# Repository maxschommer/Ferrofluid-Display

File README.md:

# Ferrofluid-Display
Ferrofluid Screen with capability of remote control boat driving.

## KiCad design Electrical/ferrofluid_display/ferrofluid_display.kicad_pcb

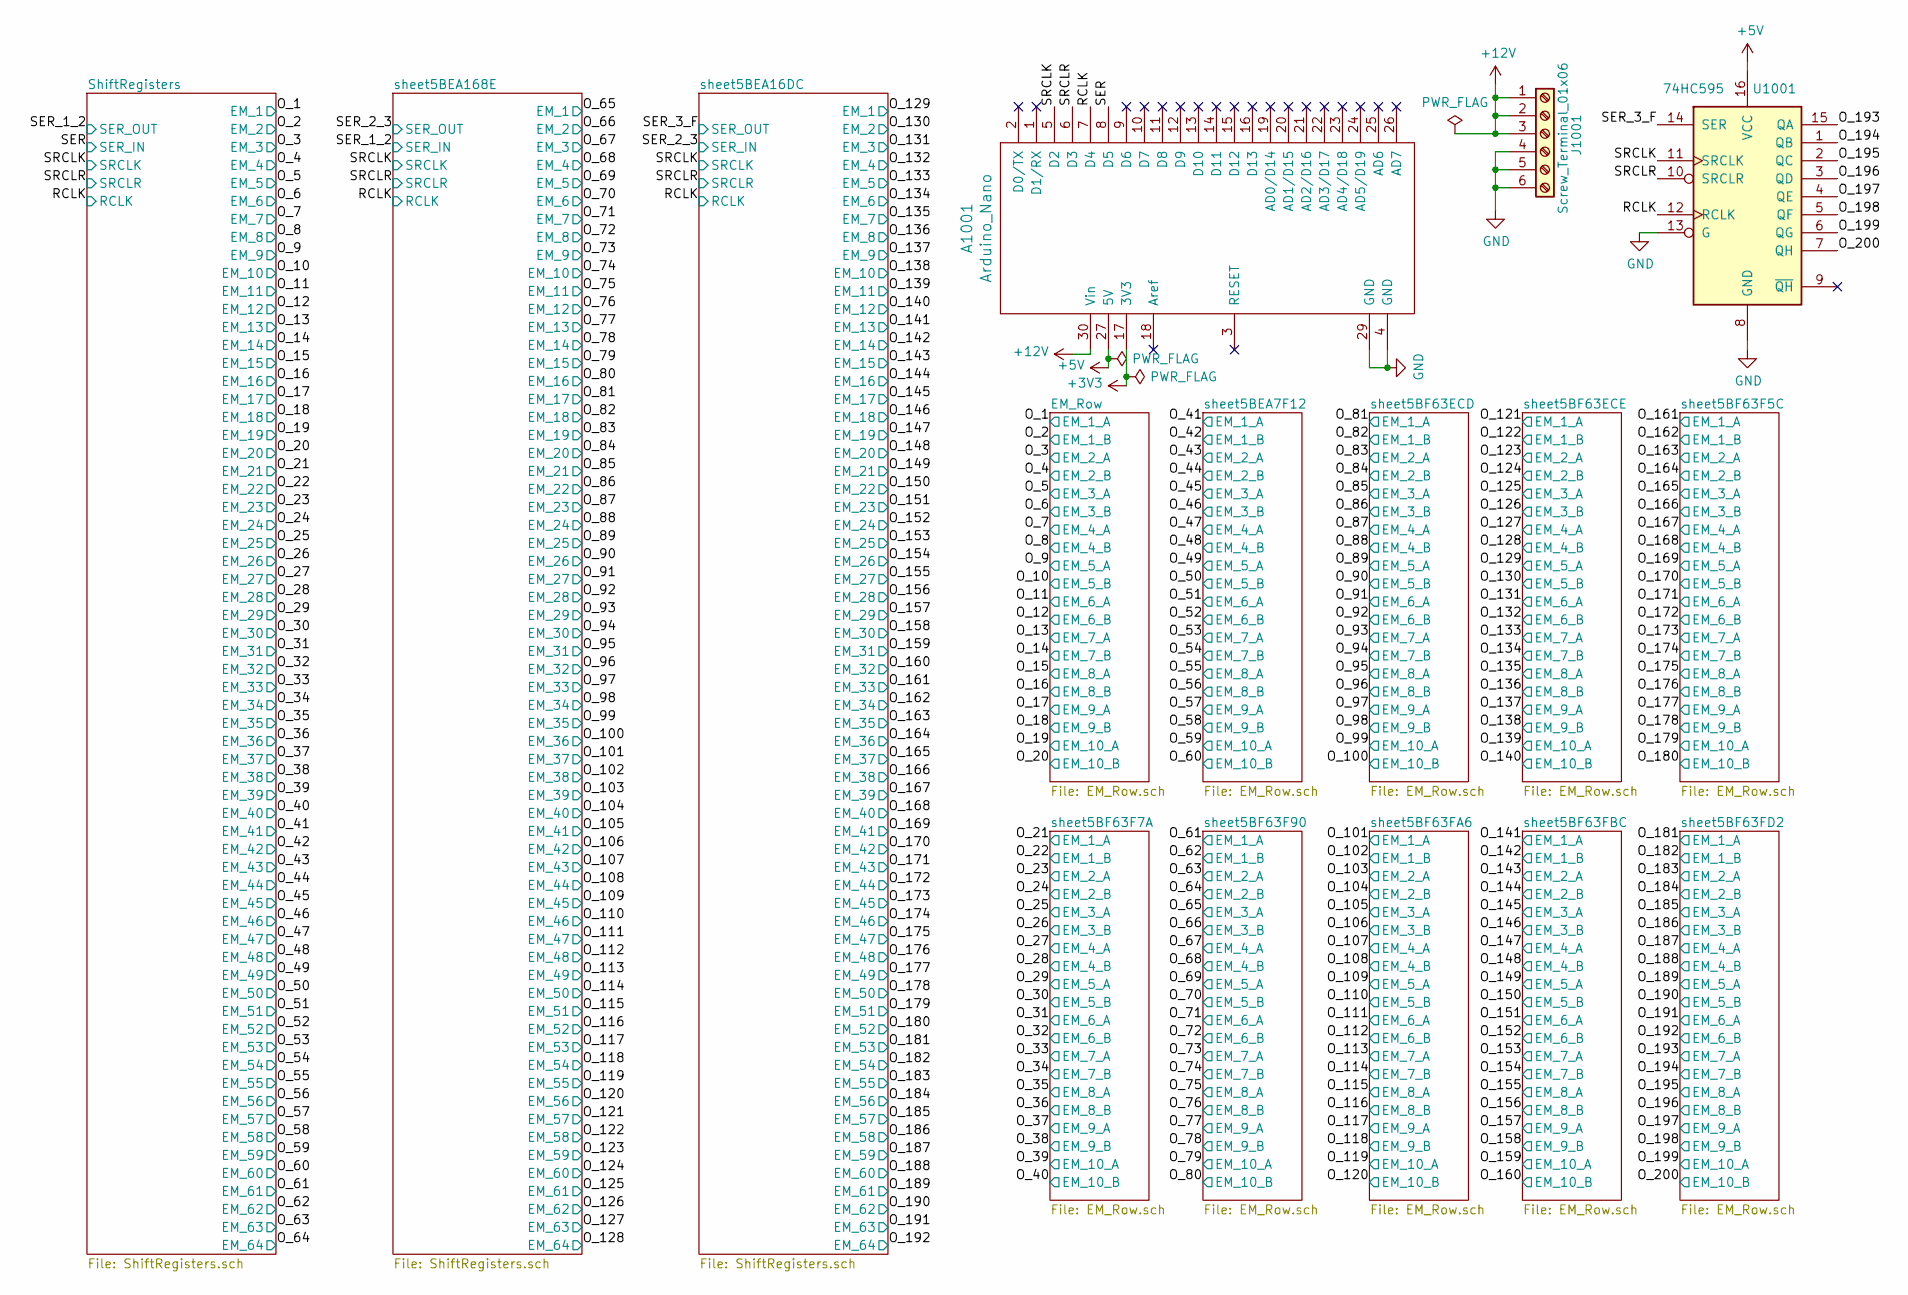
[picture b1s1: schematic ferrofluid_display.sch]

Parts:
A1001: Arduino_Nano
J1001: Screw_Terminal_01x06; 399700106
U1001: 74HC595; 74HC595D

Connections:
+3V3: A1001.17 (3V3)
+5V: A1001.27 (5V), U1001.16 (VCC); also elsewhere on the board
+12V: A1001.30 (Vin), J1001.1, J1001.2, J1001.3; also elsewhere on the board
/O_193: U1001.15 (QA); also elsewhere on the board
/O_194: U1001.1 (QB); also elsewhere on the board
/O_195: U1001.2 (QC); also elsewhere on the board
/O_196: U1001.3 (QD); also elsewhere on the board
/O_197: U1001.4 (QE); also elsewhere on the board
/O_198: U1001.5 (QF); also elsewhere on the board
/O_199: U1001.6 (QG); also elsewhere on the board
/O_200: U1001.7 (QH); also elsewhere on the board
/RCLK: A1001.7 (D4), U1001.12 (RCLK); also elsewhere on the board
/SER: A1001.8 (D5); also elsewhere on the board
/SER_3_F: U1001.14 (SER); also elsewhere on the board
/SRCLK: A1001.5 (D2), U1001.11 (SRCLK); also elsewhere on the board
/SRCLR: A1001.6 (D3), U1001.10 (SRCLR); also elsewhere on the board
GND: A1001.4 (GND), A1001.29 (GND), J1001.4, J1001.5, J1001.6, U1001.8 (GND), U1001.13 (G); also elsewhere on the board

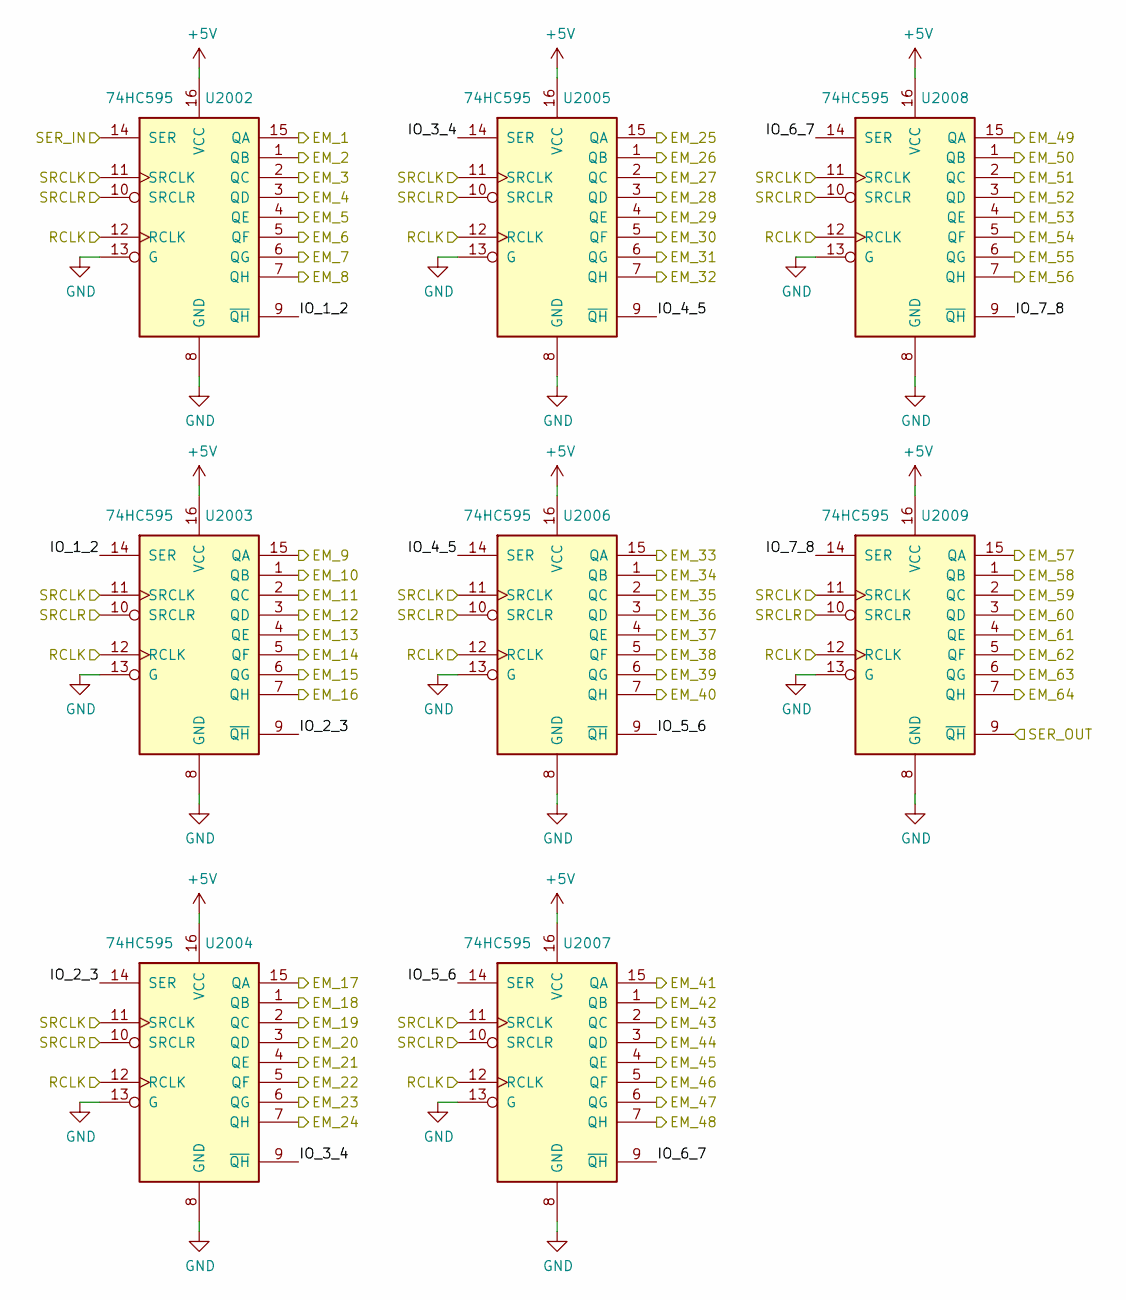
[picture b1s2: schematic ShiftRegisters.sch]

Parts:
U2002, U2003, U2004, U2005, U2006, U2007, U2008, U2009: 74HC595; 74HC595D

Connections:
+5V: U2002.16 (VCC), U2003.16 (VCC), U2004.16 (VCC), U2005.16 (VCC), U2006.16 (VCC), U2007.16 (VCC), U2008.16 (VCC), U2009.16 (VCC); also elsewhere on the board
/O_1: U2002.15 (QA); also elsewhere on the board
/O_2: U2002.1 (QB); also elsewhere on the board
/O_3: U2002.2 (QC); also elsewhere on the board
/O_4: U2002.3 (QD); also elsewhere on the board
/O_5: U2002.4 (QE); also elsewhere on the board
/O_6: U2002.5 (QF); also elsewhere on the board
/O_7: U2002.6 (QG); also elsewhere on the board
/O_8: U2002.7 (QH); also elsewhere on the board
/O_9: U2003.15 (QA); also elsewhere on the board
/O_10: U2003.1 (QB); also elsewhere on the board
/O_11: U2003.2 (QC); also elsewhere on the board
/O_12: U2003.3 (QD); also elsewhere on the board
/O_13: U2003.4 (QE); also elsewhere on the board
/O_14: U2003.5 (QF); also elsewhere on the board
/O_15: U2003.6 (QG); also elsewhere on the board
/O_16: U2003.7 (QH); also elsewhere on the board
/O_17: U2004.15 (QA); also elsewhere on the board
/O_18: U2004.1 (QB); also elsewhere on the board
/O_19: U2004.2 (QC); also elsewhere on the board
/O_20: U2004.3 (QD); also elsewhere on the board
/O_21: U2004.4 (QE); also elsewhere on the board
/O_22: U2004.5 (QF); also elsewhere on the board
/O_23: U2004.6 (QG); also elsewhere on the board
/O_24: U2004.7 (QH); also elsewhere on the board
/O_25: U2005.15 (QA); also elsewhere on the board
/O_26: U2005.1 (QB); also elsewhere on the board
/O_27: U2005.2 (QC); also elsewhere on the board
/O_28: U2005.3 (QD); also elsewhere on the board
/O_29: U2005.4 (QE); also elsewhere on the board
/O_30: U2005.5 (QF); also elsewhere on the board
/O_31: U2005.6 (QG); also elsewhere on the board
/O_32: U2005.7 (QH); also elsewhere on the board
/O_33: U2006.15 (QA); also elsewhere on the board
/O_34: U2006.1 (QB); also elsewhere on the board
/O_35: U2006.2 (QC); also elsewhere on the board
/O_36: U2006.3 (QD); also elsewhere on the board
/O_37: U2006.4 (QE); also elsewhere on the board
/O_38: U2006.5 (QF); also elsewhere on the board
/O_39: U2006.6 (QG); also elsewhere on the board
/O_40: U2006.7 (QH); also elsewhere on the board
/O_41: U2007.15 (QA); also elsewhere on the board
/O_42: U2007.1 (QB); also elsewhere on the board
/O_43: U2007.2 (QC); also elsewhere on the board
/O_44: U2007.3 (QD); also elsewhere on the board
/O_45: U2007.4 (QE); also elsewhere on the board
/O_46: U2007.5 (QF); also elsewhere on the board
/O_47: U2007.6 (QG); also elsewhere on the board
/O_48: U2007.7 (QH); also elsewhere on the board
/O_49: U2008.15 (QA); also elsewhere on the board
/O_50: U2008.1 (QB); also elsewhere on the board
/O_51: U2008.2 (QC); also elsewhere on the board
/O_52: U2008.3 (QD); also elsewhere on the board
/O_53: U2008.4 (QE); also elsewhere on the board
/O_54: U2008.5 (QF); also elsewhere on the board
/O_55: U2008.6 (QG); also elsewhere on the board
/O_56: U2008.7 (QH); also elsewhere on the board
/O_57: U2009.15 (QA); also elsewhere on the board
/O_58: U2009.1 (QB); also elsewhere on the board
/O_59: U2009.2 (QC); also elsewhere on the board
/O_60: U2009.3 (QD); also elsewhere on the board
/O_61: U2009.4 (QE); also elsewhere on the board
/O_62: U2009.5 (QF); also elsewhere on the board
/O_63: U2009.6 (QG); also elsewhere on the board
/O_64: U2009.7 (QH); also elsewhere on the board
/RCLK: U2002.12 (RCLK), U2003.12 (RCLK), U2004.12 (RCLK), U2005.12 (RCLK), U2006.12 (RCLK), U2007.12 (RCLK), U2008.12 (RCLK), U2009.12 (RCLK); also elsewhere on the board
/SER: U2002.14 (SER); also elsewhere on the board
/SER_1_2: U2009.9 (~QH); also elsewhere on the board
/SRCLK: U2002.11 (SRCLK), U2003.11 (SRCLK), U2004.11 (SRCLK), U2005.11 (SRCLK), U2006.11 (SRCLK), U2007.11 (SRCLK), U2008.11 (SRCLK), U2009.11 (SRCLK); also elsewhere on the board
/SRCLR: U2002.10 (SRCLR), U2003.10 (SRCLR), U2004.10 (SRCLR), U2005.10 (SRCLR), U2006.10 (SRCLR), U2007.10 (SRCLR), U2008.10 (SRCLR), U2009.10 (SRCLR); also elsewhere on the board
/ShiftRegisters/IO_1_2: U2002.9 (~QH), U2003.14 (SER)
/ShiftRegisters/IO_2_3: U2003.9 (~QH), U2004.14 (SER)
/ShiftRegisters/IO_3_4: U2004.9 (~QH), U2005.14 (SER)
/ShiftRegisters/IO_4_5: U2005.9 (~QH), U2006.14 (SER)
/ShiftRegisters/IO_5_6: U2006.9 (~QH), U2007.14 (SER)
/ShiftRegisters/IO_6_7: U2007.9 (~QH), U2008.14 (SER)
/ShiftRegisters/IO_7_8: U2008.9 (~QH), U2009.14 (SER)
GND: U2002.8 (GND), U2002.13 (G), U2003.8 (GND), U2003.13 (G), U2004.8 (GND), U2004.13 (G), U2005.8 (GND), U2005.13 (G), U2006.8 (GND), U2006.13 (G), U2007.8 (GND), U2007.13 (G), U2008.8 (GND), U2008.13 (G), U2009.8 (GND), U2009.13 (G); also elsewhere on the board

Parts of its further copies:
U3002, U3003, U3004, U3005, U3006, U3007, U3008, U3009, U4002, U4003, U4004, U4005, U4006, U4007, U4008, U4009: 74HC595; 74HC595D

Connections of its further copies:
+5V: U3002.16 (VCC), U3003.16 (VCC), U3004.16 (VCC), U3005.16 (VCC), U3006.16 (VCC), U3007.16 (VCC), U3008.16 (VCC), U3009.16 (VCC), U4002.16 (VCC), U4003.16 (VCC), U4004.16 (VCC), U4005.16 (VCC), U4006.16 (VCC), U4007.16 (VCC), U4008.16 (VCC), U4009.16 (VCC); also elsewhere on the board
/O_65: U3002.15 (QA); also elsewhere on the board
/O_66: U3002.1 (QB); also elsewhere on the board
/O_67: U3002.2 (QC); also elsewhere on the board
/O_68: U3002.3 (QD); also elsewhere on the board
/O_69: U3002.4 (QE); also elsewhere on the board
/O_70: U3002.5 (QF); also elsewhere on the board
/O_71: U3002.6 (QG); also elsewhere on the board
/O_72: U3002.7 (QH); also elsewhere on the board
/O_73: U3003.15 (QA); also elsewhere on the board
/O_74: U3003.1 (QB); also elsewhere on the board
/O_75: U3003.2 (QC); also elsewhere on the board
/O_76: U3003.3 (QD); also elsewhere on the board
/O_77: U3003.4 (QE); also elsewhere on the board
/O_78: U3003.5 (QF); also elsewhere on the board
/O_79: U3003.6 (QG); also elsewhere on the board
/O_80: U3003.7 (QH); also elsewhere on the board
/O_81: U3004.15 (QA); also elsewhere on the board
/O_82: U3004.1 (QB); also elsewhere on the board
/O_83: U3004.2 (QC); also elsewhere on the board
/O_84: U3004.3 (QD); also elsewhere on the board
/O_85: U3004.4 (QE); also elsewhere on the board
/O_86: U3004.5 (QF); also elsewhere on the board
/O_87: U3004.6 (QG); also elsewhere on the board
/O_88: U3004.7 (QH); also elsewhere on the board
/O_89: U3005.15 (QA); also elsewhere on the board
/O_90: U3005.1 (QB); also elsewhere on the board
/O_91: U3005.2 (QC); also elsewhere on the board
/O_92: U3005.3 (QD); also elsewhere on the board
/O_93: U3005.4 (QE); also elsewhere on the board
/O_94: U3005.5 (QF); also elsewhere on the board
/O_95: U3005.6 (QG); also elsewhere on the board
/O_96: U3005.7 (QH); also elsewhere on the board
/O_97: U3006.15 (QA); also elsewhere on the board
/O_98: U3006.1 (QB); also elsewhere on the board
/O_99: U3006.2 (QC); also elsewhere on the board
/O_100: U3006.3 (QD); also elsewhere on the board
/O_101: U3006.4 (QE); also elsewhere on the board
/O_102: U3006.5 (QF); also elsewhere on the board
/O_103: U3006.6 (QG); also elsewhere on the board
/O_104: U3006.7 (QH); also elsewhere on the board
/O_105: U3007.15 (QA); also elsewhere on the board
/O_106: U3007.1 (QB); also elsewhere on the board
/O_107: U3007.2 (QC); also elsewhere on the board
/O_108: U3007.3 (QD); also elsewhere on the board
/O_109: U3007.4 (QE); also elsewhere on the board
/O_110: U3007.5 (QF); also elsewhere on the board
/O_111: U3007.6 (QG); also elsewhere on the board
/O_112: U3007.7 (QH); also elsewhere on the board
/O_113: U3008.15 (QA); also elsewhere on the board
/O_114: U3008.1 (QB); also elsewhere on the board
/O_115: U3008.2 (QC); also elsewhere on the board
/O_116: U3008.3 (QD); also elsewhere on the board
/O_117: U3008.4 (QE); also elsewhere on the board
/O_118: U3008.5 (QF); also elsewhere on the board
/O_119: U3008.6 (QG); also elsewhere on the board
/O_120: U3008.7 (QH); also elsewhere on the board
/O_121: U3009.15 (QA); also elsewhere on the board
/O_122: U3009.1 (QB); also elsewhere on the board
/O_123: U3009.2 (QC); also elsewhere on the board
/O_124: U3009.3 (QD); also elsewhere on the board
/O_125: U3009.4 (QE); also elsewhere on the board
/O_126: U3009.5 (QF); also elsewhere on the board
/O_127: U3009.6 (QG); also elsewhere on the board
/O_128: U3009.7 (QH); also elsewhere on the board
/O_129: U4002.15 (QA); also elsewhere on the board
/O_130: U4002.1 (QB); also elsewhere on the board
/O_131: U4002.2 (QC); also elsewhere on the board
/O_132: U4002.3 (QD); also elsewhere on the board
/O_133: U4002.4 (QE); also elsewhere on the board
/O_134: U4002.5 (QF); also elsewhere on the board
/O_135: U4002.6 (QG); also elsewhere on the board
/O_136: U4002.7 (QH); also elsewhere on the board
/O_137: U4003.15 (QA); also elsewhere on the board
/O_138: U4003.1 (QB); also elsewhere on the board
/O_139: U4003.2 (QC); also elsewhere on the board
/O_140: U4003.3 (QD); also elsewhere on the board
/O_141: U4003.4 (QE); also elsewhere on the board
/O_142: U4003.5 (QF); also elsewhere on the board
/O_143: U4003.6 (QG); also elsewhere on the board
/O_144: U4003.7 (QH); also elsewhere on the board
/O_145: U4004.15 (QA); also elsewhere on the board
/O_146: U4004.1 (QB); also elsewhere on the board
/O_147: U4004.2 (QC); also elsewhere on the board
/O_148: U4004.3 (QD); also elsewhere on the board
/O_149: U4004.4 (QE); also elsewhere on the board
/O_150: U4004.5 (QF); also elsewhere on the board
/O_151: U4004.6 (QG); also elsewhere on the board
/O_152: U4004.7 (QH); also elsewhere on the board
/O_153: U4005.15 (QA); also elsewhere on the board
/O_154: U4005.1 (QB); also elsewhere on the board
/O_155: U4005.2 (QC); also elsewhere on the board
/O_156: U4005.3 (QD); also elsewhere on the board
/O_157: U4005.4 (QE); also elsewhere on the board
/O_158: U4005.5 (QF); also elsewhere on the board
/O_159: U4005.6 (QG); also elsewhere on the board
/O_160: U4005.7 (QH); also elsewhere on the board
/O_161: U4006.15 (QA); also elsewhere on the board
/O_162: U4006.1 (QB); also elsewhere on the board
/O_163: U4006.2 (QC); also elsewhere on the board
/O_164: U4006.3 (QD); also elsewhere on the board
/O_165: U4006.4 (QE); also elsewhere on the board
/O_166: U4006.5 (QF); also elsewhere on the board
/O_167: U4006.6 (QG); also elsewhere on the board
/O_168: U4006.7 (QH); also elsewhere on the board
/O_169: U4007.15 (QA); also elsewhere on the board
/O_170: U4007.1 (QB); also elsewhere on the board
/O_171: U4007.2 (QC); also elsewhere on the board
/O_172: U4007.3 (QD); also elsewhere on the board
/O_173: U4007.4 (QE); also elsewhere on the board
/O_174: U4007.5 (QF); also elsewhere on the board
/O_175: U4007.6 (QG); also elsewhere on the board
/O_176: U4007.7 (QH); also elsewhere on the board
/O_177: U4008.15 (QA); also elsewhere on the board
/O_178: U4008.1 (QB); also elsewhere on the board
/O_179: U4008.2 (QC); also elsewhere on the board
/O_180: U4008.3 (QD); also elsewhere on the board
/O_181: U4008.4 (QE); also elsewhere on the board
/O_182: U4008.5 (QF); also elsewhere on the board
/O_183: U4008.6 (QG); also elsewhere on the board
/O_184: U4008.7 (QH); also elsewhere on the board
/O_185: U4009.15 (QA); also elsewhere on the board
/O_186: U4009.1 (QB); also elsewhere on the board
/O_187: U4009.2 (QC); also elsewhere on the board
/O_188: U4009.3 (QD); also elsewhere on the board
/O_189: U4009.4 (QE); also elsewhere on the board
/O_190: U4009.5 (QF); also elsewhere on the board
/O_191: U4009.6 (QG); also elsewhere on the board
/O_192: U4009.7 (QH); also elsewhere on the board
/RCLK: U3002.12 (RCLK), U3003.12 (RCLK), U3004.12 (RCLK), U3005.12 (RCLK), U3006.12 (RCLK), U3007.12 (RCLK), U3008.12 (RCLK), U3009.12 (RCLK), U4002.12 (RCLK), U4003.12 (RCLK), U4004.12 (RCLK), U4005.12 (RCLK), U4006.12 (RCLK), U4007.12 (RCLK), U4008.12 (RCLK), U4009.12 (RCLK); also elsewhere on the board
/SER_1_2: U3002.14 (SER); also elsewhere on the board
/SER_2_3: U3009.9 (~QH), U4002.14 (SER)
/SER_3_F: U4009.9 (~QH); also elsewhere on the board
/SRCLK: U3002.11 (SRCLK), U3003.11 (SRCLK), U3004.11 (SRCLK), U3005.11 (SRCLK), U3006.11 (SRCLK), U3007.11 (SRCLK), U3008.11 (SRCLK), U3009.11 (SRCLK), U4002.11 (SRCLK), U4003.11 (SRCLK), U4004.11 (SRCLK), U4005.11 (SRCLK), U4006.11 (SRCLK), U4007.11 (SRCLK), U4008.11 (SRCLK), U4009.11 (SRCLK); also elsewhere on the board
/SRCLR: U3002.10 (SRCLR), U3003.10 (SRCLR), U3004.10 (SRCLR), U3005.10 (SRCLR), U3006.10 (SRCLR), U3007.10 (SRCLR), U3008.10 (SRCLR), U3009.10 (SRCLR), U4002.10 (SRCLR), U4003.10 (SRCLR), U4004.10 (SRCLR), U4005.10 (SRCLR), U4006.10 (SRCLR), U4007.10 (SRCLR), U4008.10 (SRCLR), U4009.10 (SRCLR); also elsewhere on the board
/sheet5BEA16DC/IO_1_2: U4002.9 (~QH), U4003.14 (SER)
/sheet5BEA16DC/IO_2_3: U4003.9 (~QH), U4004.14 (SER)
/sheet5BEA16DC/IO_3_4: U4004.9 (~QH), U4005.14 (SER)
/sheet5BEA16DC/IO_4_5: U4005.9 (~QH), U4006.14 (SER)
/sheet5BEA16DC/IO_5_6: U4006.9 (~QH), U4007.14 (SER)
/sheet5BEA16DC/IO_6_7: U4007.9 (~QH), U4008.14 (SER)
/sheet5BEA16DC/IO_7_8: U4008.9 (~QH), U4009.14 (SER)
/sheet5BEA168E/IO_1_2: U3002.9 (~QH), U3003.14 (SER)
/sheet5BEA168E/IO_2_3: U3003.9 (~QH), U3004.14 (SER)
/sheet5BEA168E/IO_3_4: U3004.9 (~QH), U3005.14 (SER)
/sheet5BEA168E/IO_4_5: U3005.9 (~QH), U3006.14 (SER)
/sheet5BEA168E/IO_5_6: U3006.9 (~QH), U3007.14 (SER)
/sheet5BEA168E/IO_6_7: U3007.9 (~QH), U3008.14 (SER)
/sheet5BEA168E/IO_7_8: U3008.9 (~QH), U3009.14 (SER)
GND: U3002.8 (GND), U3002.13 (G), U3003.8 (GND), U3003.13 (G), U3004.8 (GND), U3004.13 (G), U3005.8 (GND), U3005.13 (G), U3006.8 (GND), U3006.13 (G), U3007.8 (GND), U3007.13 (G), U3008.8 (GND), U3008.13 (G), U3009.8 (GND), U3009.13 (G), U4002.8 (GND), U4002.13 (G), U4003.8 (GND), U4003.13 (G), U4004.8 (GND), U4004.13 (G), U4005.8 (GND), U4005.13 (G), U4006.8 (GND), U4006.13 (G), U4007.8 (GND), U4007.13 (G), U4008.8 (GND), U4008.13 (G), U4009.8 (GND), U4009.13 (G); also elsewhere on the board

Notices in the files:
parts and their libraries:
Copyright 2016 Accelerated Designs. All rights reserved.
